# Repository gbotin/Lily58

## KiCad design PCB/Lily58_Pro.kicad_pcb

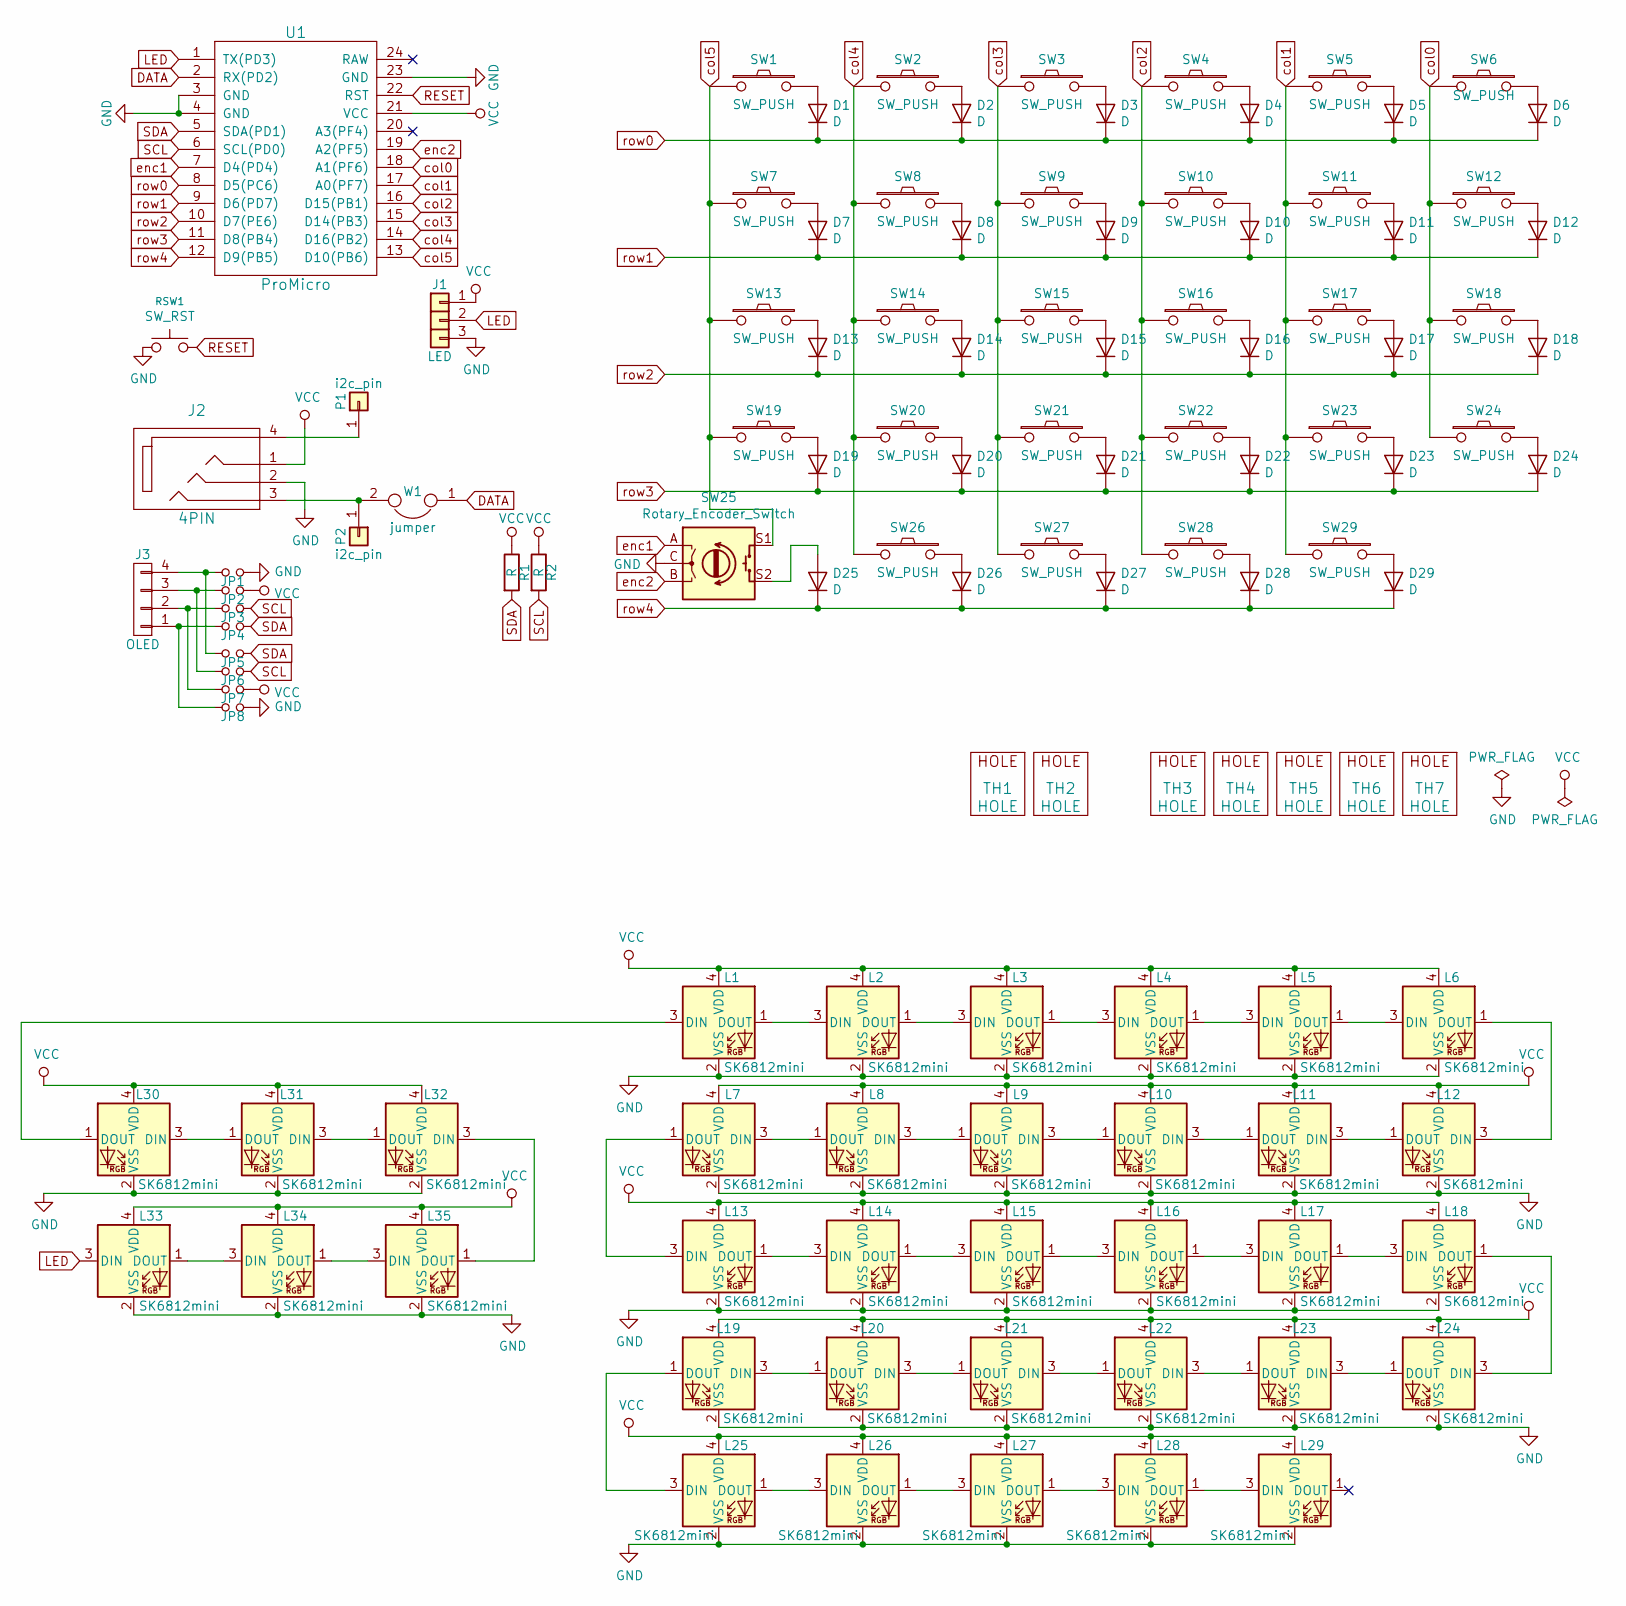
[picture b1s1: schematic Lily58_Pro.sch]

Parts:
D1, D2, D3, D4, D5, D6, D7, D8, D9, D10, D11, D12, D13, D14, D15, D16, D17, D18, D19, D20, D21, D22, D23, D24, D25, D26, D27, D28, D29: D; Diode_SOD123
J1: LED
J2: 4PIN; MJ-4PP-9
J3: OLED; OLED_4Pin
JP1, JP2, JP3, JP4, JP5, JP6, JP7, JP8: Jumper_NO_Small; Jumper
L1, L2, L3, L4, L5, L6, L7, L8, L9, L10, L11, L12, L13, L14, L15, L16, L17, L18, L19, L20, L21, L22, L23, L24, L25, L26, L27, L28, L29: SK6812mini; SK6812MINI
L30, L31, L32, L33, L34, L35: SK6812mini; SK6812MINI_underglow
P1, P2: i2c_pin; 1pin_conn
R1, R2: R; RESISTOR_mini
RSW1: SW_RST; TACT_SWITCH_TVBP06
SW1, SW2, SW3, SW4, SW5, SW6, SW7, SW8, SW9, SW10, SW11, SW12, SW13, SW14, SW15, SW16, SW17, SW18, SW19, SW20, SW21, SW22, SW23, SW24, SW26, SW27, SW28, SW29: SW_PUSH; MX_Choc_Hotswap
SW25: Rotary_Encoder_Switch; RotaryEncoder_optional
TH1, TH2: HOLE; M2_HOLE_PCB
TH3, TH4, TH5, TH6, TH7: HOLE; HOLE_M2_TH
U1: ProMicro; ProMicro_rev2
W1: jumper; SolderJumper-2_P1.3mm_Bridged_Pad1.0x1.5mm

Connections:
DATA: U1.2 (RX(PD2)), W1.1
GND: J1.3, J2.2, JP1.2, JP8.2, L1.2 (VSS), L2.2 (VSS), L3.2 (VSS), L4.2 (VSS), L5.2 (VSS), L6.2 (VSS), L7.2 (VSS), L8.2 (VSS), L9.2 (VSS), L10.2 (VSS), L11.2 (VSS), L12.2 (VSS), L13.2 (VSS), L14.2 (VSS), L15.2 (VSS), L16.2 (VSS), L17.2 (VSS), L18.2 (VSS), L19.2 (VSS), L20.2 (VSS), L21.2 (VSS), L22.2 (VSS), L23.2 (VSS), L24.2 (VSS), L25.2 (VSS), L26.2 (VSS), L27.2 (VSS), L28.2 (VSS), L29.2 (VSS), L30.2 (VSS), L31.2 (VSS), L32.2 (VSS), L33.2 (VSS), L34.2 (VSS), L35.2 (VSS), RSW1.1, SW25.C, U1.3 (GND), U1.4 (GND), U1.23 (GND)
LED: J1.2, L33.3 (DIN), U1.1 (TX(PD3))
unnamed: D1.2 (A), SW1.2
unnamed: D2.2 (A), SW2.2
unnamed: D3.2 (A), SW3.2
unnamed: D4.2 (A), SW4.2
unnamed: D5.2 (A), SW5.2
unnamed: D6.2 (A), SW6.2
unnamed: D7.2 (A), SW7.2
unnamed: D8.2 (A), SW8.2
unnamed: D9.2 (A), SW9.2
unnamed: D10.2 (A), SW10.2
unnamed: D11.2 (A), SW11.2
unnamed: D12.2 (A), SW12.2
unnamed: D13.2 (A), SW13.2
unnamed: D14.2 (A), SW14.2
unnamed: D15.2 (A), SW15.2
unnamed: D16.2 (A), SW16.2
unnamed: D17.2 (A), SW17.2
unnamed: D18.2 (A), SW18.2
unnamed: D19.2 (A), SW19.2
unnamed: D20.2 (A), SW20.2
unnamed: D21.2 (A), SW21.2
unnamed: D22.2 (A), SW22.2
unnamed: D23.2 (A), SW23.2
unnamed: D24.2 (A), SW24.2
unnamed: D26.2 (A), SW26.2
unnamed: D27.2 (A), SW27.2
unnamed: D28.2 (A), SW28.2
unnamed: D29.2 (A), SW29.2
unnamed: J2.3, P2.1, W1.2
unnamed: J2.4, P1.1
unnamed: J3.1, JP4.1, JP8.1
unnamed: J3.2, JP3.1, JP7.1
unnamed: J3.3, JP2.1, JP6.1
unnamed: J3.4, JP1.1, JP5.1
unnamed: L1.1 (DOUT), L2.3 (DIN)
unnamed: L1.3 (DIN), L30.1 (DOUT)
unnamed: L2.1 (DOUT), L3.3 (DIN)
unnamed: L3.1 (DOUT), L4.3 (DIN)
unnamed: L4.1 (DOUT), L5.3 (DIN)
unnamed: L5.1 (DOUT), L6.3 (DIN)
unnamed: L7.3 (DIN), L8.1 (DOUT)
unnamed: L8.3 (DIN), L9.1 (DOUT)
unnamed: L9.3 (DIN), L10.1 (DOUT)
unnamed: L10.3 (DIN), L11.1 (DOUT)
unnamed: L11.3 (DIN), L12.1 (DOUT)
unnamed: L6.1 (DOUT), L12.3 (DIN)
unnamed: L13.1 (DOUT), L14.3 (DIN)
unnamed: L7.1 (DOUT), L13.3 (DIN)
unnamed: L14.1 (DOUT), L15.3 (DIN)
unnamed: L15.1 (DOUT), L16.3 (DIN)
unnamed: L16.1 (DOUT), L17.3 (DIN)
unnamed: L17.1 (DOUT), L18.3 (DIN)
unnamed: L18.1 (DOUT), L24.3 (DIN)
unnamed: L19.1 (DOUT), L25.3 (DIN)
unnamed: L19.3 (DIN), L20.1 (DOUT)
unnamed: L20.3 (DIN), L21.1 (DOUT)
unnamed: L21.3 (DIN), L22.1 (DOUT)
unnamed: L22.3 (DIN), L23.1 (DOUT)
unnamed: L23.3 (DIN), L24.1 (DOUT)
unnamed: L25.1 (DOUT), L26.3 (DIN)
unnamed: L26.1 (DOUT), L27.3 (DIN)
unnamed: L27.1 (DOUT), L28.3 (DIN)
unnamed: L28.1 (DOUT), L29.3 (DIN)
unnamed: L30.3 (DIN), L31.1 (DOUT)
unnamed: L31.3 (DIN), L32.1 (DOUT)
unnamed: L32.3 (DIN), L35.1 (DOUT)
unnamed: L33.1 (DOUT), L34.3 (DIN)
unnamed: L34.1 (DOUT), L35.3 (DIN)
RESET: RSW1.2, U1.22 (RST)
SCL: JP3.2, JP6.2, R2.2, U1.6 (SCL(PD0))
SDA: JP4.2, JP5.2, R1.2, U1.5 (SDA(PD1))
VCC: J1.1, J2.1, JP2.2, JP7.2, L1.4 (VDD), L2.4 (VDD), L3.4 (VDD), L4.4 (VDD), L5.4 (VDD), L6.4 (VDD), L7.4 (VDD), L8.4 (VDD), L9.4 (VDD), L10.4 (VDD), L11.4 (VDD), L12.4 (VDD), L13.4 (VDD), L14.4 (VDD), L15.4 (VDD), L16.4 (VDD), L17.4 (VDD), L18.4 (VDD), L19.4 (VDD), L20.4 (VDD), L21.4 (VDD), L22.4 (VDD), L23.4 (VDD), L24.4 (VDD), L25.4 (VDD), L26.4 (VDD), L27.4 (VDD), L28.4 (VDD), L29.4 (VDD), L30.4 (VDD), L31.4 (VDD), L32.4 (VDD), L33.4 (VDD), L34.4 (VDD), L35.4 (VDD), R1.1, R2.1, U1.21 (VCC)
col0: SW6.1, SW12.1, SW18.1, SW24.1, U1.18 (A1(PF6))
col1: SW5.1, SW11.1, SW17.1, SW23.1, SW29.1, U1.17 (A0(PF7))
col2: SW4.1, SW10.1, SW16.1, SW22.1, SW28.1, U1.16 (D15(PB1))
col3: SW3.1, SW9.1, SW15.1, SW21.1, SW27.1, U1.15 (D14(PB3))
col4: SW2.1, SW8.1, SW14.1, SW20.1, SW26.1, U1.14 (D16(PB2))
col5: SW1.1, SW7.1, SW13.1, SW19.1, SW25.1, SW25.S1, U1.13 (D10(PB6))
enc1: SW25.A, U1.7 (D4(PD4))
enc2: SW25.B, U1.19 (A2(PF5))
row0: D1.1 (K), D2.1 (K), D3.1 (K), D4.1 (K), D5.1 (K), D6.1 (K), U1.8 (D5(PC6))
row1: D7.1 (K), D8.1 (K), D9.1 (K), D10.1 (K), D11.1 (K), D12.1 (K), U1.9 (D6(PD7))
row2: D13.1 (K), D14.1 (K), D15.1 (K), D16.1 (K), D17.1 (K), D18.1 (K), U1.10 (D7(PE6))
row3: D19.1 (K), D20.1 (K), D21.1 (K), D22.1 (K), D23.1 (K), D24.1 (K), U1.11 (D8(PB4))
row4: D25.1 (K), D26.1 (K), D27.1 (K), D28.1 (K), D29.1 (K), U1.12 (D9(PB5))

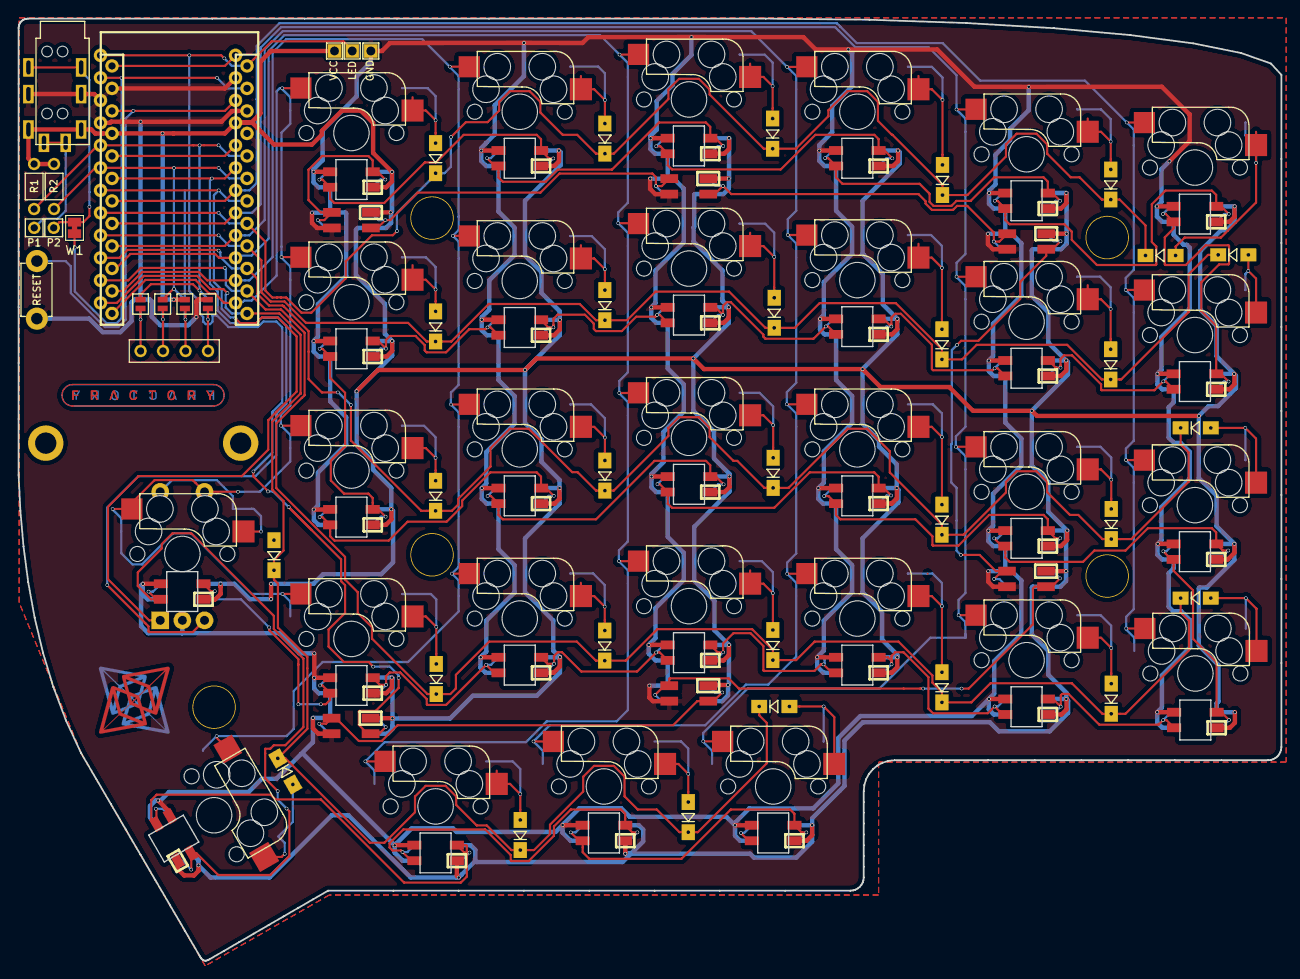
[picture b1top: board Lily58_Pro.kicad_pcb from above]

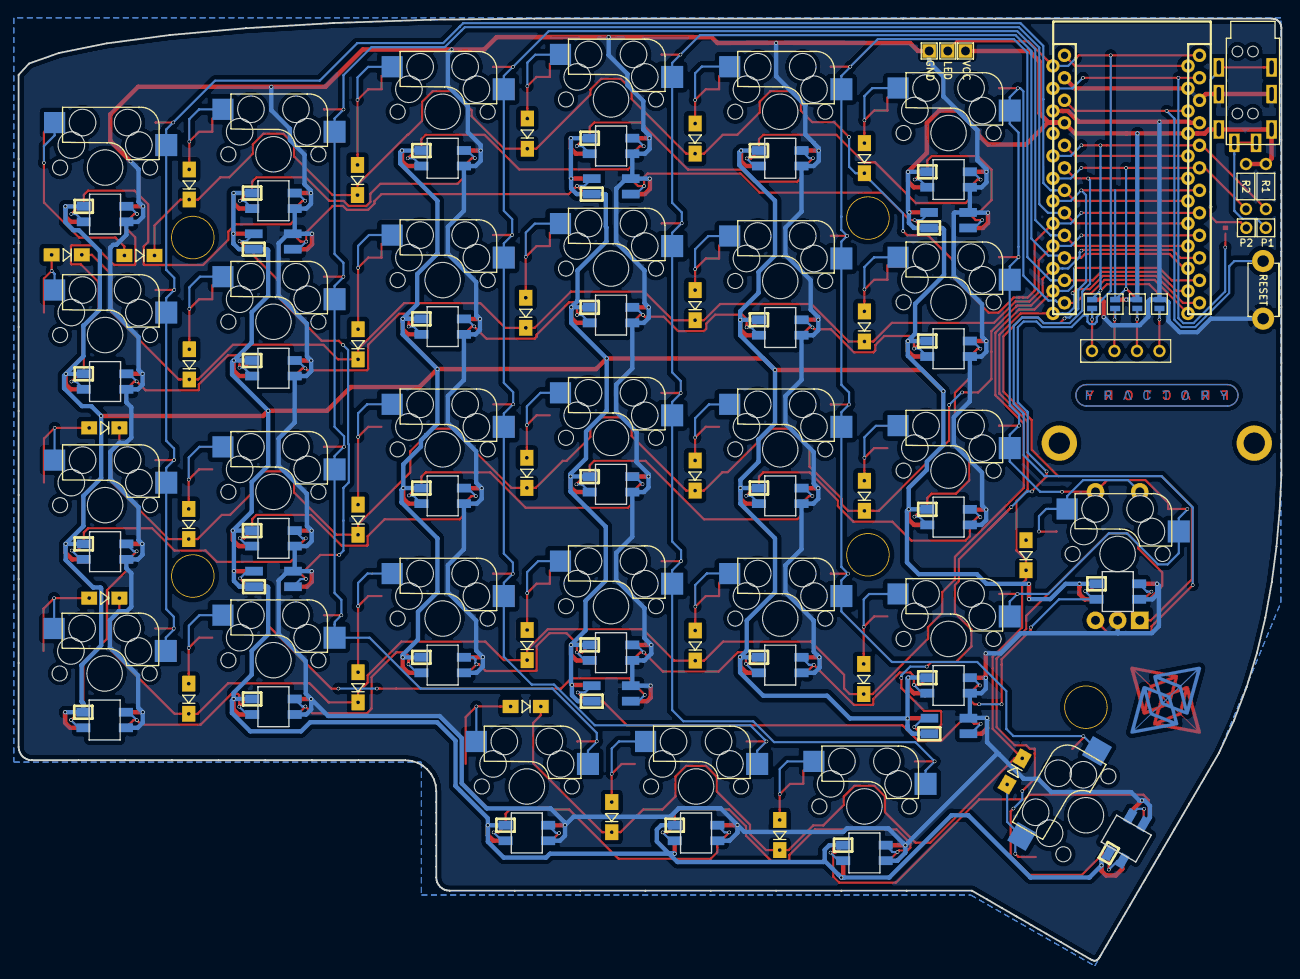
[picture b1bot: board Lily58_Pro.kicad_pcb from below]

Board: 2 copper layers, 142.5 x 106.3 mm, 128 parts (8 on the bottom side), 88 nets.

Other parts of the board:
G1, G2, G5: LOGO; LOGO_NAME_SMALL_copper
G3, G4, G6: LOGO; LOGO_NAME_SMALL_mask
G10, G12: LOGO; LOGO_MEDIUM_copper
G11, G13: LOGO; LOGO_MEDIUM_mask

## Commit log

2020-07-04 Cleanup
2020-07-05 Remove choc support & cleanup tracks
2020-07-05 Fix switch drill holes
2020-07-05 Add rotary encoder
2020-07-05 Update schematics with rgb backlight/underglow
2020-07-05 WIP underglow/backlight
2020-07-13 Finishing underglow/backlight
2020-07-14 WIP net
2020-07-14 WIP net (cols)
2020-07-14 WIP net (rows)
2020-07-14 WIP net (leds)
2020-07-14 Aestetics
2020-07-14 Net done
2020-07-14 Finishing
